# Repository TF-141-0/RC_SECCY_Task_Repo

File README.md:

# RC_SECCY_Task_Repo
Y24 recruitment Task and solutions

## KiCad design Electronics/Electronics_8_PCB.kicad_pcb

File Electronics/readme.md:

# PCB Design Task – Arduino Nano + MPU9250 + Power Regulation + LEDs

## Objective
Design a PCB circuit that includes the following components:

- Arduino Nano
- MPU9250 IMU Sensor Module
- Voltage Regulator to provide a stable 5V output from a 3S Li-ion battery pack  
  (11.1V nominal, made of 18650 cells)
- Two LEDs

---

## Deliverables

The schematic and PCB layout must ensure proper, logical, and real-world-ready electrical connections between all components. This includes best practices like:
- Pull-up resistors (e.g., for I²C)
- Decoupling capacitors
- Stable power routing
- Grounding discipline

---

### 1. Schematic Diagram (30 Points)
- Clean and well-organized schematic
- Proper component names and designators (e.g., R1, C2, U1)
- Labels for all net connections (e.g., VCC, GND, SDA, SCL)
- Fully logical and complete circuit for functional behavior

---

### 2. PCB Layout and Gerber Files (70 Points)
- Compact, clean layout on a single or double-layer PCB
- Good routing practices:
  - Short trace lengths
  - Proper signal/power separation
  - Solid grounding
- Perform and pass DRC (Design Rule Check)
- Export manufacturer-ready Gerber files

---

## Final Submission Should Include:
- Schematic.pdf
- Project.kicad_pcb
- Gerber/ directory with all layer files
- Optional: 3D renders or BOM (.csv) if available

---

Note: Use KiCad or a compatible open-source EDA tool.

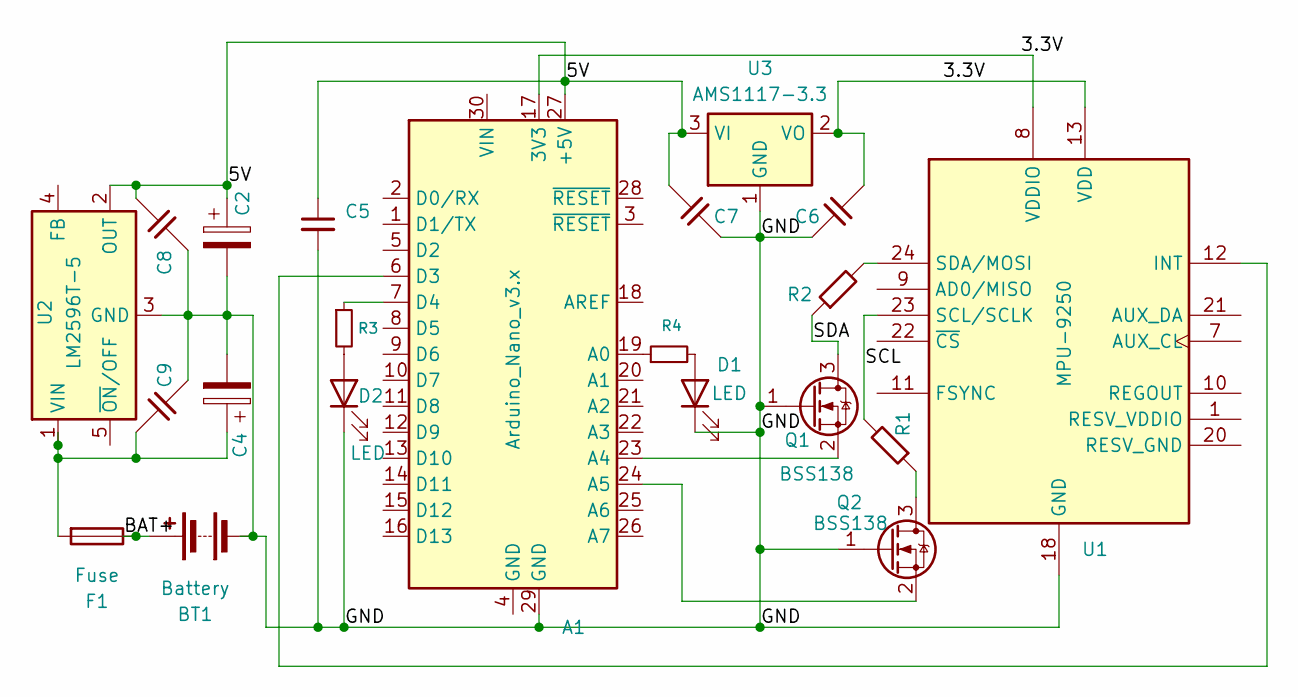
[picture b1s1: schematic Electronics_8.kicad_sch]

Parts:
A1: Arduino_Nano_v3.x; Arduino_Nano
BT1: Battery
C2, C4: C_Polarized
C5: C_Small
C6, C7, C8, C9: C_45deg
D1, D2: LED
F1: Fuse
Q1, Q2: BSS138; SOT-23
R1, R2: R_45deg
R3, R4: R_Small
U1: MPU-9250; InvenSense_QFN-24_3x3mm_P0.4mm
U2: LM2596T-5; TO-220-5_P3.4x3.7mm_StaggerOdd_Lead3.8mm_Vertical
U3: AMS1117-3.3; SOT-223-3_TabPin2

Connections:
/3.3V: A1.17 (3V3), C6.1, U1.8 (VDDIO), U1.13 (VDD), U3.2 (VO)
/5V: A1.27 (+5V), C2.1, C5.1, C7.2, C8.1, U2.2 (OUT), U3.3 (VI)
/BAT+: BT1.1 (+), F1.1
/GND: A1.29 (GND), BT1.2 (-), C2.2, C4.2, C5.2, C6.2, C7.1, C8.2, C9.1, D1.1 (K), D2.1 (K), Q1.1 (G), Q2.1 (G), U1.18 (GND), U2.3 (GND), U3.1 (GND)
/SCL: R1.2, U1.23 (SCL/SCLK)
/SDA: Q1.3 (D), R2.1
unnamed: A1.19 (A0), R4.1
unnamed: A1.23 (A4), Q1.2 (S)
unnamed: A1.24 (A5), Q2.2 (S)
unnamed: A1.6 (D3), U1.12 (INT)
unnamed: A1.7 (D4), R3.1
unnamed: D1.2 (A), R4.2
unnamed: D2.2 (A), R3.2
unnamed: Q2.3 (D), R1.1
unnamed: R2.2, U1.24 (SDA/MOSI)
unnamed: C4.1, C9.2, F1.2, U2.1 (VIN)

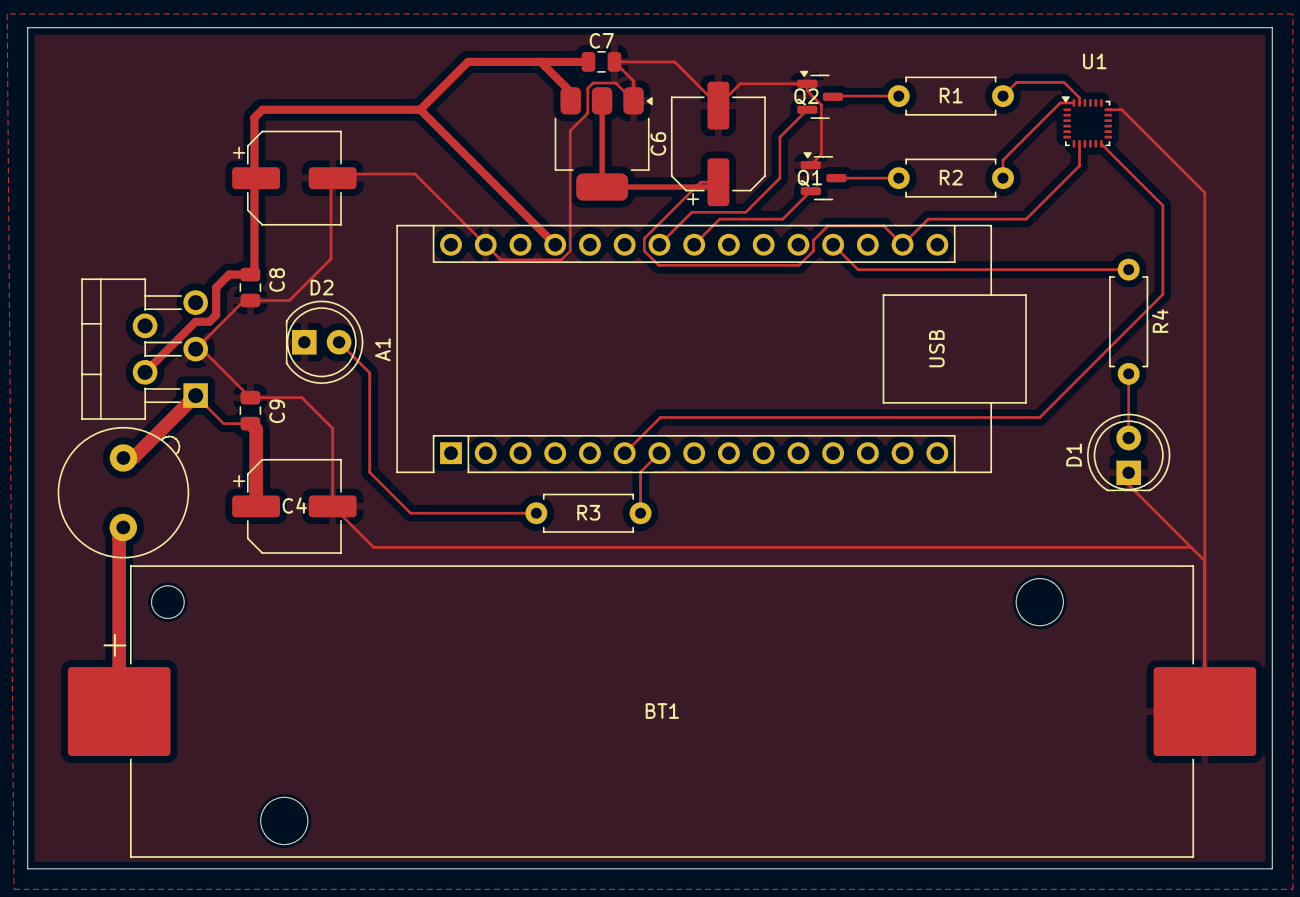
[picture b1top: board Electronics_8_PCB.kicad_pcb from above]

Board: 2 copper layers, 91.0 x 61.5 mm, 20 parts (0 on the bottom side), 16 nets.

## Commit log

2025-05-16 Create Mechanical_Task
2025-05-16 Rename Mech_2.tex to Mechanical_2.tex
2025-05-16 Rename Software_5.txt to Software_5.C
2025-05-23 Rename Problem_statement.md to readme.md
